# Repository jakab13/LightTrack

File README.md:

# LightTrack

**LightTrack** is a simple, Arduino-controlled LED response track for behavioural and psychophysics experiments.

The original prototype was developed for auditory distance-estimation experiments at Leipzig University's [Neurobiology Group](https://www.lw.uni-leipzig.de/en/institut-fuer-biologie/abteilungen/general-zoology-and-neurobiology/research). Participants moved a red marker along two floor-mounted LED strips with an Xbox controller and pressed A to confirm their response. The system was later further developed at TU Berlin's [Audio Communication Group](https://www.tu.berlin/ak) for another auditory distance experiment at the [Faculty of Media Sciences](https://www.hs-mittweida.de/en/about-us/faculty-media-sciences/) of Mittweida University of Applied Sciences.

<p align="center"><em>The LightTrack controller: an Arduino Nano R4 on a small carrier board, housed in a 3D-printed enclosure.</em></p>

---

## Files

The implementation is intentionally small:

Python keeps track of the participant's current response, converts that distance to the nearest LED position, and sends the corresponding command to an Arduino. The Arduino only controls the LED strips.

- `lighttrack.py` - Python interface to the response track
- `lighttrack/lighttrack.ino` - Arduino firmware
- `experiment_example.py` - small auditory distance-estimation example
- `experiment_mittweida.py` - auditory distance experiment that sends the responses via OSC
- `quicktest.py` - checks the connection, the controller and the LEDs
- `requirements.txt` - Python dependencies
- `hardware/pcb-board/` - KiCad 10 schematic and PCB of the controller board
- `hardware/enclosure/` - Blender model of the controller enclosure

---

## Wiring

The default Arduino pins in `lighttrack/lighttrack.ino` are:

```cpp
LEFT_PIN = 6
RIGHT_PIN = 7
```

The two strips should be installed in the **same direction**, with LED 0 at the start of the response track.

Wiring of the controller board (`hardware/pcb-board/`):

In the assembled controller, the panel-mount DC jack is wired to J1; J2 and J3 lead to the two JST sockets in the enclosure wall; J4 is reachable through the slot in the wall for power injection.

The Arduino and the LED power supply must share a **common ground**.

Do not power a long LED strip from the Arduino itself. Use an external regulated 5 V power supply. For long physical installations, power may need to be supplied at more than one point along the strip. Power injection is provided on the PCB.
In our tests with two 20 m strips (30 LEDs/m), power injection was not needed.

---

## Arduino setup

1. Install the [Arduino IDE](https://www.arduino.cc/en/software).
2. Install the [Adafruit NeoPixel library](https://github.com/adafruit/Adafruit_NeoPixel).
3. Open `lighttrack/lighttrack.ino`.
4. Check that `LEFT_PIN` and `RIGHT_PIN` match your wiring.
5. Upload the sketch to the Arduino.

### Command line alternative

With [arduino-cli](https://arduino.github.io/arduino-cli/) installed, the `Makefile` builds and flashes the firmware.
The board core and library versions in `lighttrack/sketch.yaml` are installed automatically on the first build.

```bash
make compile   # build only
make upload    # build and flash (port is auto-detected, or pass PORT=/dev/cu.usbmodem101)
make monitor   # serial monitor at 115200 baud
make flash     # upload, then open the serial monitor
make ports     # list connected boards
```

The Arduino does not need to know the physical distance range. Python sends the required number of LED positions when it connects.

---

## Python setup

Install the required packages:

```bash
pip install -r requirements.txt
```

The main LightTrack settings are defined in metres:

```python
from lighttrack import LightTrack

track = LightTrack(
    port="COM5",
    start_m=1,
    end_m=13,
    leds_per_m=30,
)
```

On macOS or Linux, the serial port may look more like:

```python
port="/dev/cu.usbmodem101"
```

### Basic use

```python
track.show(7.0)       # red marker at approximately 7 m
track.confirm()       # current marker turns green

track.clear()
track.close()
```

The experimenter never needs to work directly with LED numbers.

For example, with:

```python
start_m = 1
end_m = 13
leds_per_m = 30
```

LightTrack automatically maps:

```text
1 m   -> beginning of the track
7 m   -> middle of the track
13 m  -> end of the track
```

If a requested position falls between two LEDs, the nearest physical LED is used.

---

## Quick test

`quicktest.py` checks that the connection, the controller and the LEDs work.
The serial port, the track length and the marker speed are set at the top of the script.

```bash
python quicktest.py
```

What it does:

1. connects to LightTrack (1 m to 20 m, 30 LEDs/m);
2. uses the first controller pygame finds.
   Without a controller it opens a small window and uses the keyboard: the Up and Down arrows act like the joystick, Space acts like A;
3. shows a red marker in the middle of the track.
   The joystick (or the arrow keys) moves it continuously, the D-pad moves it in 0.1 m steps;
4. A (or Space) turns the marker green to confirm the position.
   It turns red again as soon as the marker moves.

The script prints the controller name, every position where the marker stops and every confirmed position.
Stop it with Ctrl+C in the terminal or by closing the pygame window.
The LEDs are switched off when the script stops.

Check that:

- both strips show a single marker;
- both markers indicate the same physical position;
- the marker moves in the expected direction;
- confirmation changes the marker to green.

---

## Troubleshooting

### No LEDs turn on

Check:

- the external 5 V supply;
- common ground between Arduino and LED supply;
- LED strip `DIN` rather than `DOUT`;
- Arduino serial port;
- whether `lighttrack/lighttrack.ino` was uploaded successfully.

### Arduino connects, but LEDs do not respond

Check:

- the data wires from J2 (left strip, D6) and J3 (right strip, D7) to each strip's `DIN`;
- the solder joints of the data line resistors R1 and R2;
- that the strip is WS2812B-compatible;
- that the Arduino and Python code both use 115200 baud.

### Only one strip works

Check the second strip's:

- data wire;
- 5 V connection;
- ground connection.

### Position does not match the physical track

Check:

```python
start_m
end_m
leds_per_m
```

Also verify where the first physical LED sits relative to the start of the distance scale.

### LEDs behave unreliably

Check the power wiring first: the 5 V supply at J1, the common ground and that C1 is fitted with the correct polarity.
Long strips may require additional power injection via J4.

---

## Parts list

This list contains all parts that are needed to build the LightTrack system. (This does NOT include any spare parts!)

| Qty                           | Part                                                 | What it does                                                                                                              | Example / helper                                                                                                                                                              |
| ----------------------------- | ---------------------------------------------------- | ------------------------------------------------------------------------------------------------------------------------- | ----------------------------------------------------------------------------------------------------------------------------------------------------------------------------- |
| 1                             | **Arduino Nano R4**                                  | Receives serial commands from Python and controls the LEDs                                                                | Version without headers (ABX00142) - soldering is fun.<br>If you order the one with preinstalled headers, you do not need to order the next part in this list                 |
| 2&nbsp;×&nbsp;15 pins         | **Pin headers, 2.54 mm**                             | Soldered to the Nano so it can be plugged into the socket strips                                                          | You can order longer strips and cut them to length                                                                                                                            |
| 2&nbsp;×&nbsp;15 pins         | **Female socket strips, 2.54 mm, 8.5 mm high**       | Hold the Nano on the PCB, so it can be swapped without desoldering                                                        | Same goes here                                                                                                                                                                |
| 1                             | **Controller PCB**                                   | Carrier board for the Nano, the resistors, the capacitor and all screw terminals                                          | Manufactured from the KiCad files in `hardware/pcb-board/`                                                                                                                    |
| 1&nbsp;+&nbsp;2&nbsp;+&nbsp;1 | **Screw terminals, 5.08 mm, 90°** (2-, 3- and 4-pin) | 5 V input (J1), left and right LED strip (J2, J3), power injection (J4)                                                   |                                                                                                                                                                               |
| 2                             | **470 Ω resistor**                                   | Series resistor in each LED data line (R1, R2)                                                                            |                                                                                                                                                                               |
| 1                             | **1.5 kΩ resistor**                                  | Current limit for the supply indicator LED (R3)                                                                           |                                                                                                                                                                               |
| 1                             | **3 mm green LED, low current (2 mA)**               | Shows that the 5 V LED supply is present (D1)                                                                             |                                                                                                                                                                               |
| 1                             | **1000 µF / 25 V electrolytic capacitor**            | Stabilises the LED supply (C1)                                                                                            |                                                                                                                                                                               |
| 1                             | **5 V / 4 A power supply**, 5.5 × 2.1 mm plug        | Powers the LED strips                                                                                                     | e.g. MEAN WELL GST25E05-P1J                                                                                                                                                   |
| 1                             | **Panel-mount DC jack**, 5.5 × 2.1 mm                | Power input in the enclosure wall, wired to J1                                                                            | Needs an 11 mm panel hole, solder lugs                                                                                                                                        |
| 4 pairs                       | **JST SM connectors, 3-pin**                         | Plug the LED strips into the enclosure via an adapter cable                                                               | SMP-03V-BC in the enclosure wall and on each strip, adapter cable with SMR-03V-B on both ends;<br>plus crimp contacts (3 × SHF-001T-0.8BS per SMP, 3 × SYM-001T-P0.6 per SMR) |
| 1                             | **3D-printed enclosure** (base + lid)                | Houses the controller PCB                                                                                                 | Print from the Blender project `lighttrack_enclosure.blend` in `hardware/enclosure/`                                                                                          |
| 8&nbsp;×&nbsp;5&nbsp;m        | **WS2812B LED strip, 30 LEDs/m**                     | Displays the response position: 4 rolls joined per strip, 2 strips of 20 m (600 LEDs each, 571 used for the 1-20 m track) | e.g. [example LED strip](https://www.adafruit.com/product/2537) - order as many as YOU need for your project                                                                  |
| 4                             | **M3 × 10 self-tapping screws**, pan head            | Hold the lid on the base                                                                                                  |                                                                                                                                                                               |
| 4                             | **M3 × 6 self-tapping screws**                       | Hold the PCB on the standoffs                                                                                             |                                                                                                                                                                               |
| 4                             | **Rubber feet**, self-adhesive, 10 mm diameter       | Fit the recesses on the enclosure underside                                                                               | (nice to have)                                                                                                                                                                |
| ~25 mm                        | **3 mm clear acrylic rod**                           | Light pipe from the supply LED to the lid                                                                                 | (nice to have)                                                                                                                                                                |
| as needed                     | **3-core cable** (+5 V, data, GND)                   | Making adapters and leads, e.g. from the strips' JST plugs to the enclosure and from the strips to the PCB terminals      | e.g. 3 × 0.75 mm², sized for the strip current                                                                                                                                |
| as needed                     | **Hookup wire**                                      | Power injection wiring                                                                                                    | Only needed for very long LED strips                                                                                                                                          |
| 1                             | **USB-C data cable**                                 | Connects the Arduino to the experiment computer                                                                           |                                                                                                                                                                               |
| 1                             | **Game controller**                                  | Participant input in the example                                                                                          | e.g. Xbox Wireless Controller, but check out the [pygame joystick docs](https://www.pygame.org/docs/ref/joystick.html) for supported controllers                              |

### Recommended Arduino

For a new build, a **compact 5 V Arduino** is the easiest option.

The [Arduino Nano R4](https://docs.arduino.cc/hardware/nano-r4/) is a good default because it combines a small Nano-format board with **5 V GPIO** and USB-C. This makes it convenient for a small portable interface and avoids the extra logic-level conversion normally needed when a 3.3 V controller drives a 5 V LED strip.

The original LightTrack prototype used an **Arduino Nano 33 IoT**. Its small size was useful for the same portability reasons, but it uses 3.3 V GPIO. If a 3.3 V board is used, a suitable logic-level shifter is recommended.

### LED strips

LightTrack is written for individually addressable WS2812B-style RGB strips.

The original system used **30 LEDs/m**, giving a physical response resolution of about:

```text
1 / 30 m = 3.3 cm
```

The Adafruit strip linked above is only an example. Equivalent 5 V WS2812B-compatible strips from other suppliers should work as well.

For general wiring and power guidance, the [Adafruit NeoPixel Überguide](https://learn.adafruit.com/adafruit-neopixel-uberguide) and its [best-practices page](https://learn.adafruit.com/adafruit-neopixel-uberguide/best-practices) are useful references.

---

## How LightTrack fits into other experiments

LightTrack itself does not depend on auditory experiments.

The same interface can be used wherever a participant needs to indicate a position along a physical scale:

```text
controller / keyboard / other input
                ↓
          experiment code
                ↓
       response in physical units
                ↓
            LightTrack
                ↓
             Arduino
                ↓
            LED marker
```

Python remains the central hub, so the input device and stimulus software can be replaced without changing the Arduino side.

---

## Useful links

- [Arduino Nano R4 documentation](https://docs.arduino.cc/hardware/nano-r4/)
- [Arduino Nano R4 official store](https://store.arduino.cc/products/nano-r4)
- [Arduino IDE](https://www.arduino.cc/en/software)
- [Adafruit NeoPixel 30 LEDs/m example strip](https://www.adafruit.com/product/2537)
- [Adafruit NeoPixel Überguide](https://learn.adafruit.com/adafruit-neopixel-uberguide)
- [NeoPixel best practices](https://learn.adafruit.com/adafruit-neopixel-uberguide/best-practices)
- [Adafruit NeoPixel Arduino library](https://github.com/adafruit/Adafruit_NeoPixel)
- [Xbox Wireless Controller](https://www.xbox.com/accessories/controllers/xbox-wireless-controller)
- [slab](https://github.com/DrMarc/slab)
- [slab documentation](https://slab.readthedocs.io/)
- [Original distance_anchoring experiment](https://github.com/SebSchroe/distance_anchoring)

---

## License

See `LICENSE`.

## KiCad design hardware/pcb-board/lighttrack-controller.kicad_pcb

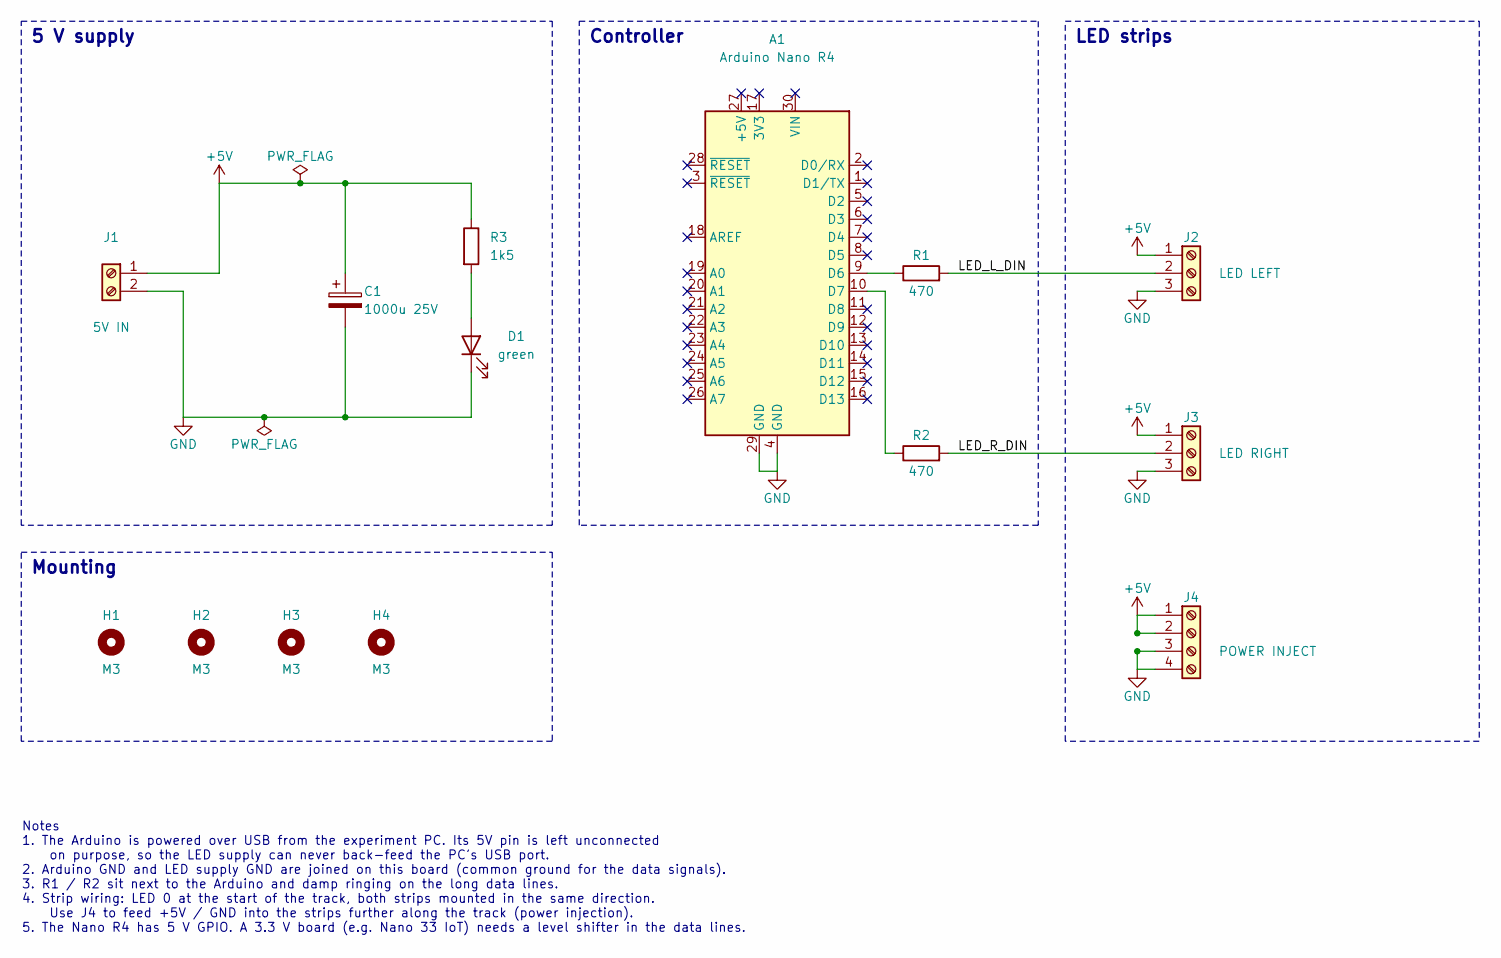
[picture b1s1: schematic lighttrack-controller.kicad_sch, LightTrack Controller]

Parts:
A1: Arduino Nano R4; Arduino_Nano_R4
C1: 1000u 25V; CP_Radial_D10.0mm_P5.00mm
D1: green; LED_D3.0mm
H1, H2, H3, H4: M3; MountingHole_3.2mm_M3
J1: 5V IN; TerminalBlock_Phoenix_MKDS-1,5-2-5.08_1x02_P5.08mm_Horizont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
J2: LED LEFT; TerminalBlock_Phoenix_MKDS-1,5-3-5.08_1x03_P5.08mm_Horizont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
J3: LED RIGHT; TerminalBlock_Phoenix_MKDS-1,5-3-5.08_1x03_P5.08mm_Horizont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
J4: POWER INJECT; TerminalBlock_Phoenix_MKDS-1,5-4-5.08_1x04_P5.08mm_Horizont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
R1, R2: 470; R_Axial_DIN0207_L6.3mm_D2.5mm_P10.16mm_Horizontal
R3: 1k5; R_Axial_DIN0207_L6.3mm_D2.5mm_P10.16mm_Horizontal

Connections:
+5V: C1.1, J1.1, J2.1, J3.1, J4.1, J4.2, R3.1
/LED_L_DIN: J2.2, R1.2
/LED_R_DIN: J3.2, R2.2
GND: A1.4 (GND), A1.29 (GND), C1.2, D1.1 (K), J1.2, J2.3, J3.3, J4.3, J4.4
unnamed: A1.9 (D6), R1.1
unnamed: A1.10 (D7), R2.1
unnamed: D1.2 (A), R3.2

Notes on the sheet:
5 V supply
Mounting
Controller
Notes 1. The Arduino is powered over USB from the experiment PC. Its 5V pin is left unconnected on purpose, so the LED supply can never back-feed the PC's USB port. 2. Arduino GND and LED supply GND are joined on this board (common ground for the data signals). 3. R1 / R2 sit next to the Arduino an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
LED strips

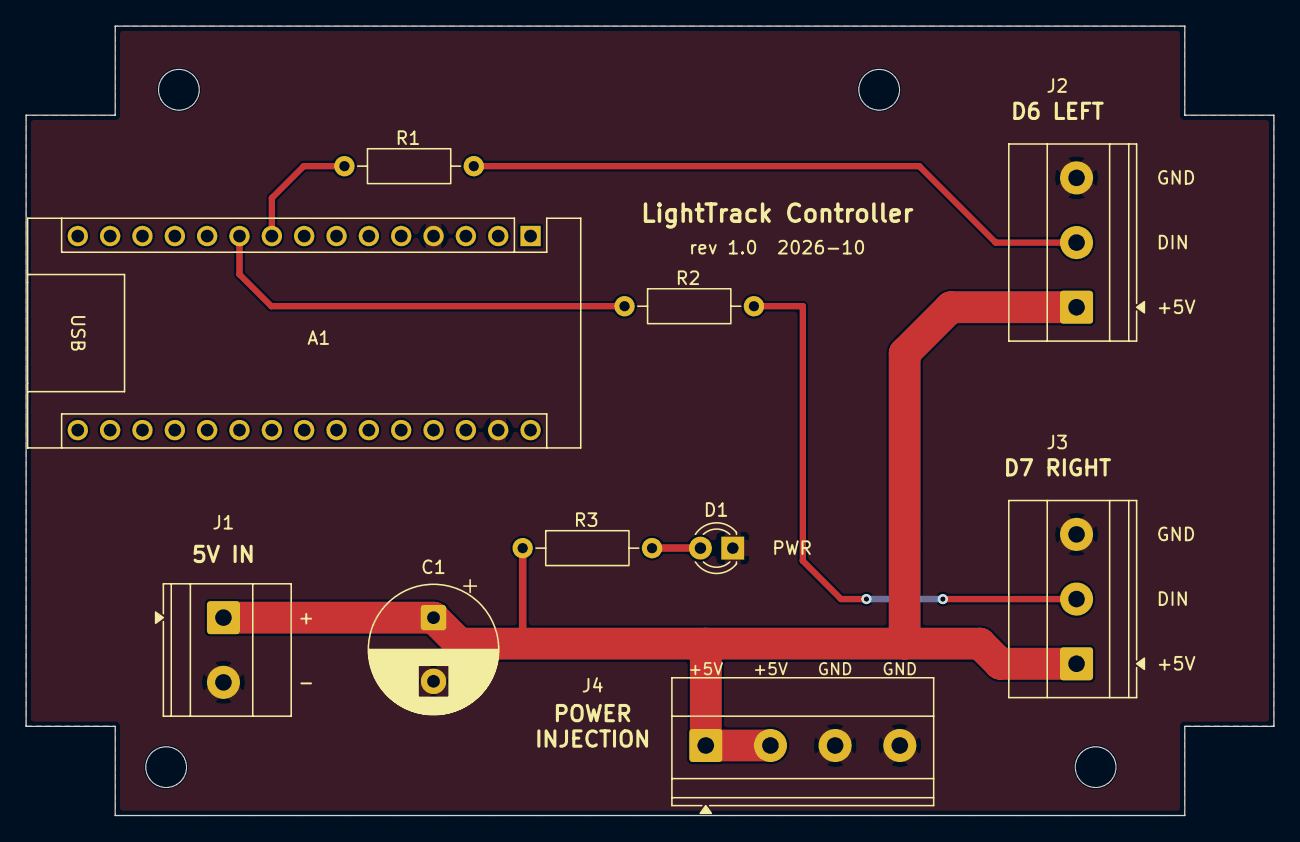
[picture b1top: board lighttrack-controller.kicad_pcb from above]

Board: 2 copper layers, 98.0 x 62.0 mm, 14 parts (0 on the bottom side), 7 nets.
